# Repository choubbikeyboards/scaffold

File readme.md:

Scaffold keyboard
=================

This keyboard is inspired by many others, among which the Ferris, the Kyria, the Dactyl Manuform, and others.
The major contribution of this project is the method of using PCB for simultaneous structural support and electrical wiring of individual keys.

Status
------

This is still pretty much a prototype. The files I provide here have not yet been made into a PCB, although a previous version with minor changes has been tested successfully for some parts, and not so much for others.
Software side is not too advanced either, and you'll have to write your own QMK keymap.c file, as I didn't write a basic QWERTY keymap yet, and mine is pretty tuned to my personal use, with combos and stuff that works only for US-International OS-side layout.
The files for QMK can be found on my personal fork of QMK (https://github.com/choubbikeyboards/qmk_firmware/tree/master/keyboards/scaffold).

Important, read before ordering the PCBs!
-----------------------------------------

These boards need special ordering procedure, in order to just have to separate the smaller parts by hand. The fab must allow you to do V-scoring on your PCB. You must ask them to do V-scoring on all PCBs, by using the CMTS layer in the .zip files provided. This will tell the fab where to cut grooves into the PCB, to allow easy hand separation. This can be more expensive but saves a lot of time and possibly health, if you were to cut into the PCB yourself in your home (glass composite dust is nasty stuff for the lungs).
For more info about V-scoring, see this page.
Quick guide for an order on JLCPCB:
* Go to jlcpcb.com
* Click "Order now" button
* Click "Add gerber file" button, and select the .zip of one of the provided .zip files
* In "Delivery Format", click "Panel by customer", this should add a new option just below: "Panel Format"
* In "Panel Format", set the number of columns and row
    * 3 cols and 1 row for `scaffold.zip`
    * 1 col and 7 rows for `scaffold_supports.zip`
    * 6 cols and 6 rows for `scaffold_small_boards.zip`
* In "Remove Order Number", click "Specify a location", except for `scaffold_small_boards.zip`
* In "PCB Remark" (you need to click the pencil to access the text box), write this text: "Please V-score on Cmts layer". This will let the fab know that you want V-scoring and where to find it.

There are 3 different Kicad projects, all of these are necessary for a 3D scaffold build:
* `scaffold/` is the main PCB, and can be used as a standalone flat keyboard.
* `scaffold_supports/` is the angled supports that position the key above the main PCB. These are angled at 27°, the lowest I could get without problems.
* `scaffold_small_boards/` is the individual key footprints, with a Kailh low-profile and an SMD diode soldered in place. These are used for angled keys only, the flat keys have their diode soldered on the main board, and the switch inserted in a Kailh low-profile socket, soldered on the back of the main PCB.

Required parts
--------------

You will need as many of these as keys you want (for a full keys keyboard, that's 42 units):
* Kailh low-profile switches
* SMD diodes (I used SOD123 diodes)
* Keycaps

* As many Kailh low-profile hot-swap sockets as you want flat keys (including thumbs!)
* 2 ProMicro compatible boards
* 1 USB cable compatible with the ProMicro board you chose
* 2 push buttons, 6x6x4.3mm type
* 2 TRRS sockets, PJ-320A compatible footprint
* 1 TRRS cable
* either a custom case if you know how to make one, or 4mm thick adhesive silione feet (about 14 for the full keyboard).

Optional, for as many joysticks as you want:
* Joycon/Switch joysticks
* 5-pin 0.5mm pitch FPC/FFC connector
* something to attach the joystick to the board:
    * double-sided tape for thumb sticks
    * 2 screws, M1.6x5mm, and 2 M1.6 nuts per index stick. Double-sided tape work well too.

Optional, for each OLED screen you want:
* 4-pin 0.96 inch 128x64 OLED screen, SSD 1306 driver
* 2 resistors, value between 3 and 5kOhms (get 4.7k if you want a definite value)

Assembly guide
--------------

NOTE: This guide shows pictures of the version 1 of the keyboard. Current version (V2) uses inside soldering for the angled supports, both for the individual PCB and the main PCB. This shouldn't add much difficulty. This was done in order to get the whole PCB structure to interact better with the switches, as the previous version required the user to push hard on a switch to make it fit (slightly deforming the small plastic legs of the switch).

This is a quick overview of how to assemble a Scaffold keyboard. It shows only the right hand half, and skips the main components (MCU, OLED and its resistors...). It also shows a 3x5 configuration. For a 4x4-1 configuration, use the angled supports only for the top and bottom key of each column, and use hotswap sockets for the switches in between.

* Optional step: you can pre-tin the pads on the PCB pieces that you will solder on the board. The current version (V2 when I edit this guide) needs only one side of the angled pieces pre-tinned, and only the underside of the key holder pieces. Just be careful not to fill the switch pin holes when doing so.
* 1st step is to separate the pieces you'll need: each angled key needs 2 angled supports and an individual key holder.
* Then, start putting solder on one of the pads of each SMD diode, for the flat keys only (so 5 keys + thumbs here for a 3x5 configuration, 7 keys + thumbs for a 4x4-1 configuration)

* Once the solder is on one pad of a diode, place the diode on its footprint (white bar of the diode where the point of the triangle meets the other bar), solder one leg to the pre-soldered pad, and once the solder has cooled down, solder the other leg. Pre-soldering the pad makes it easier to solder the first leg without having to hold the soldering wire too. Keeping the other pad clean lets the diode leg rest against the PCB.

* Don't hesitate to turn the PCB around to access the pads more comfortably! 

* Now the SMD headers for the joysticks, if you plan on mounting one. This part is quite hard for me, so you will probably be best served by generic SMD soldering guides on your video website of choice. Anyway, I start by pre-soldering the pads. Be sure to check if there aren't any shorts at this stage, and don't use too much solder, or it will spread to the other pins when pushing the pin onto the solder in the later steps.

* Place the header on its footprint. That step requires accuracy to make the next step easier. Make sure the pins are properly aligned. Use a magnifying glass if needed (I can't do it without one myself).

* Solder the sides of the header first, and adjust the position of the header if it moved. Then solder the pins by pressing on them with the hot iron for a couple seconds and release. The solder placed earlier will normally stick to the pin and the pad, connecting them.

* Check for shorts, fix until no short remains... Have I mentioned I found this part hard?

* For each of the angled keys you need, solder the diode, like has been done on the main PCB for the flat keys. Again, trust the silkscreen to see which way to solder the diode.

* now, for each angled key, you have to build the support. Start with placing 2 angled supports in the slots of a key that is near the edge of the PCB. I prefer to build the supports where the supports are shown in the picture:

* Then, place the individual support on top, with the diode on top, but near the edge closest to the main PCB (towards the center of the main PCB on that picture). Then solder the inside connections on the highest point. This makes the angled support hold its own for soldering the other inner solder joints after removing the support from the main PCB.

* Take the angled support off the main PCB, solder the remaining inner joints. Try to keep the switch pin hole free for the next step.

* In the meantime, you can solder the hotswap sockets for the flat keys.

* Back to the angled holders: push the switch all the way in (requires a bit of force, but be careful not to bend a pin), and solder the pins to the small board.

* \[Version 2: soldering is now on the inside of the "box" to attach to the main PCB. Trickier, but fewer chances of shorting two adjacent switches together and better fit of the switch in the PCB\]
Now you have to solder the angled supports to the main PCB. The order of soldering can make things a bit simpler, but there will always remain a few tricky spots to solder.

* \[Version 2 solves this problem\]
Make sure to avoid soldering 2 adjacent switches together!

* Having the flat key switches off the board makes things easier.

* You now can place the switches in the hotswap sockets, solder the rest of the elements if it's not done already, and plug the joysticks in if needed. I used dual sided tape on angled supports for the thumb joysticks, just don't put a diode on those supports. Flat index joysticks can be taped to the main PCB the same way, or bolted in place with M1.6x5mm bolts.

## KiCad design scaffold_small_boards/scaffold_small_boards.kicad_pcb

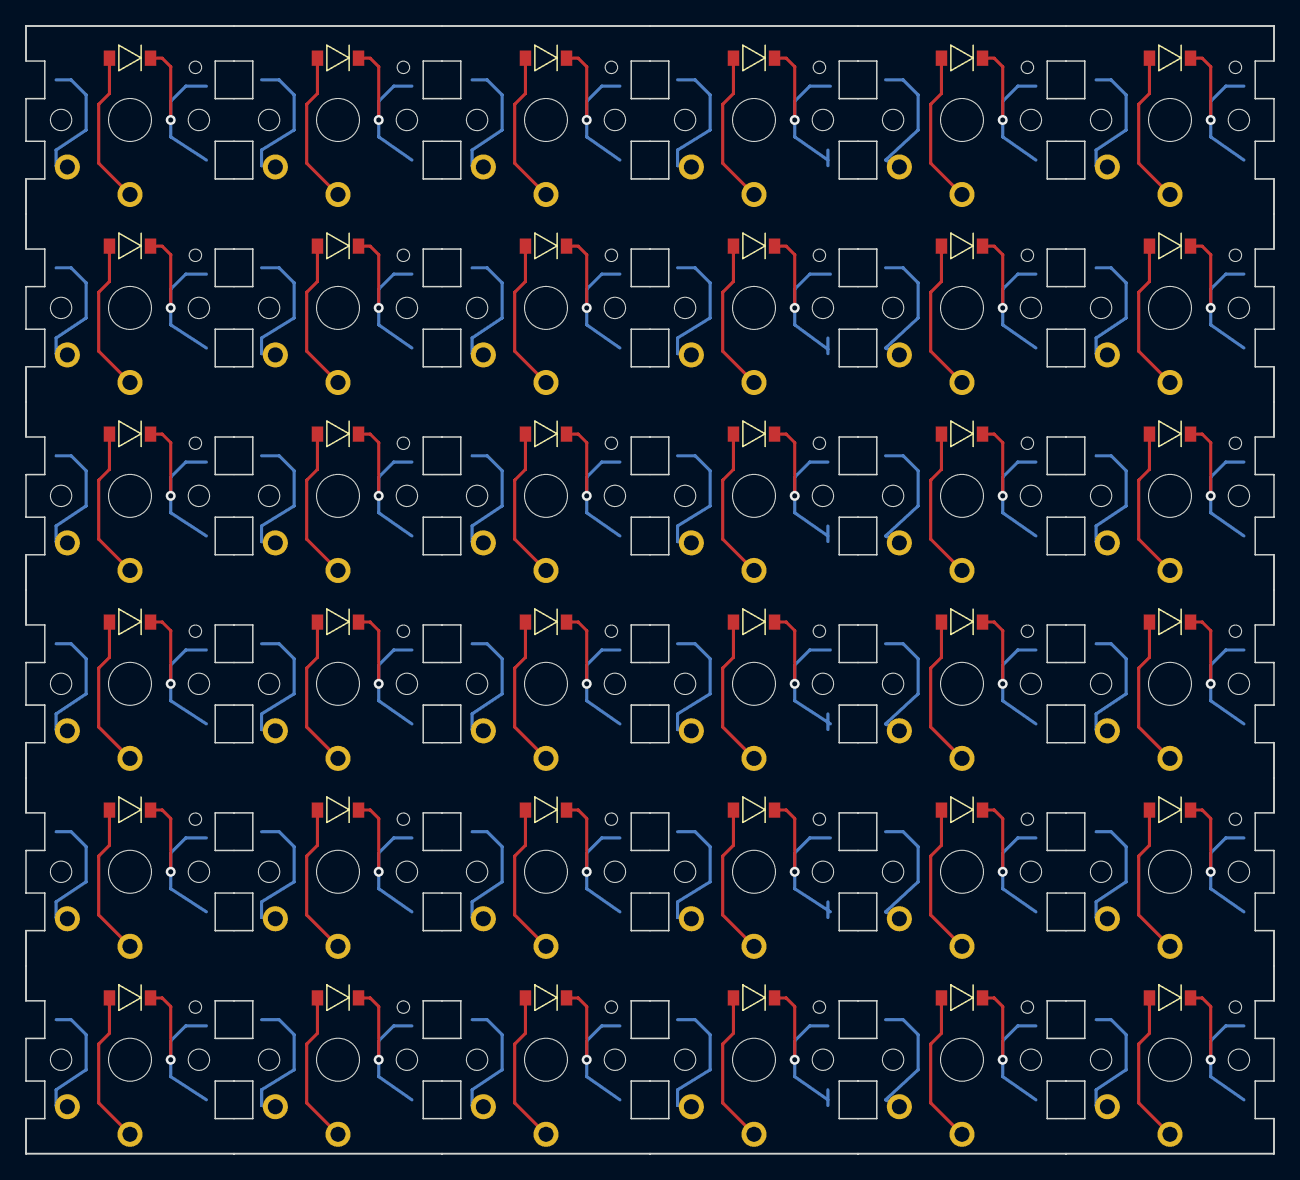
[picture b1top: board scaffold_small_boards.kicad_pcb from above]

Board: 2 copper layers, 99.6 x 90.0 mm, 36 parts (0 on the bottom side), 36 nets.

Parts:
SW_and_D1: SW_and_D; Kailh_PG1350_and_sod123_and_cutouts_top_left_v2
SW_and_D2, SW_and_D3, SW_and_D4, SW_and_D21: SW_and_D; Kailh_PG1350_and_sod123_and_cutouts_left_v2
SW_and_D5: SW_and_D; Kailh_PG1350_and_sod123_and_cutouts_bottom_left_v2
SW_and_D6, SW_and_D11, SW_and_D16, SW_and_D31: SW_and_D; Kailh_PG1350_and_sod123_and_cutouts_top_v2
SW_and_D7, SW_and_D8, SW_and_D9, SW_and_D12, SW_and_D13, SW_and_D14, SW_and_D17, SW_and_D18, SW_and_D19, SW_and_D25, SW_and_D26, SW_and_D27, SW_and_D28, SW_and_D29, SW_and_D30, SW_and_D32: SW_and_D; Kailh_PG1350_and_sod123_and_cutouts_center_v2
SW_and_D10, SW_and_D15, SW_and_D20, SW_and_D33: SW_and_D; Kailh_PG1350_and_sod123_and_cutouts_bottom_v2
SW_and_D22, SW_and_D23, SW_and_D24, SW_and_D35: SW_and_D; Kailh_PG1350_and_sod123_and_cutouts_right_v2
SW_and_D34: SW_and_D; Kailh_PG1350_and_sod123_and_cutouts_top_right_v2
SW_and_D36: SW_and_D; Kailh_PG1350_and_sod123_and_cutouts_bottom_right_v2

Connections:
unnamed: SW_and_D1.2, SW_and_D1.A
unnamed: SW_and_D2.2, SW_and_D2.A
unnamed: SW_and_D3.2, SW_and_D3.A
unnamed: SW_and_D4.2, SW_and_D4.A
unnamed: SW_and_D5.2, SW_and_D5.A
unnamed: SW_and_D6.2, SW_and_D6.A
unnamed: SW_and_D7.2, SW_and_D7.A
unnamed: SW_and_D8.2, SW_and_D8.A
unnamed: SW_and_D9.2, SW_and_D9.A
unnamed: SW_and_D10.2, SW_and_D10.A
unnamed: SW_and_D11.2, SW_and_D11.A
unnamed: SW_and_D12.2, SW_and_D12.A
unnamed: SW_and_D13.2, SW_and_D13.A
unnamed: SW_and_D14.2, SW_and_D14.A
unnamed: SW_and_D15.2, SW_and_D15.A
unnamed: SW_and_D16.2, SW_and_D16.A
unnamed: SW_and_D17.2, SW_and_D17.A
unnamed: SW_and_D18.2, SW_and_D18.A
unnamed: SW_and_D19.2, SW_and_D19.A
unnamed: SW_and_D20.2, SW_and_D20.A
unnamed: SW_and_D21.2, SW_and_D21.A
unnamed: SW_and_D22.2, SW_and_D22.A
unnamed: SW_and_D23.2, SW_and_D23.A
unnamed: SW_and_D24.2, SW_and_D24.A
unnamed: SW_and_D25.2, SW_and_D25.A
unnamed: SW_and_D26.2, SW_and_D26.A
unnamed: SW_and_D27.2, SW_and_D27.A
unnamed: SW_and_D28.2, SW_and_D28.A
unnamed: SW_and_D29.2, SW_and_D29.A
unnamed: SW_and_D30.2, SW_and_D30.A
unnamed: SW_and_D31.2, SW_and_D31.A
unnamed: SW_and_D32.2, SW_and_D32.A
unnamed: SW_and_D33.2, SW_and_D33.A
unnamed: SW_and_D34.2, SW_and_D34.A
unnamed: SW_and_D35.2, SW_and_D35.A
unnamed: SW_and_D36.2, SW_and_D36.A

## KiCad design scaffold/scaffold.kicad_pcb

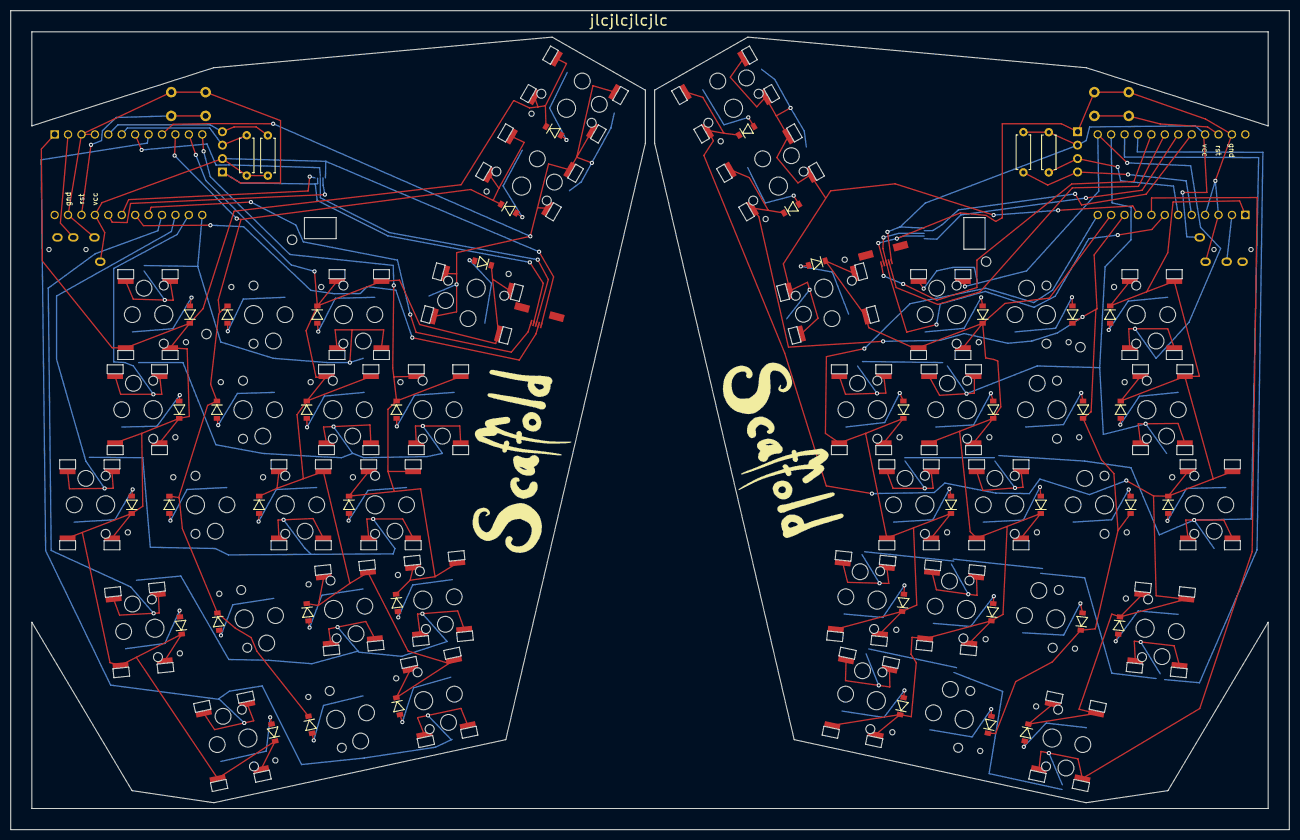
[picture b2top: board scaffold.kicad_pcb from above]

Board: 2 copper layers, 242.0 x 155.0 mm, 32 parts (0 on the bottom side), 84 nets.

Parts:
Col1, Col5: Col3; Col3_socket_PG1350_sod123_cutouts_v2
Col2, Col3, Col4: Col4; Col4_socket_PG1350_sod123_cutouts_v2
ColR1, ColR5: Col3; Col3_socket_PG1350_sod123_cutouts_v2
ColR2, ColR3, ColR4: Col4; Col4_socket_PG1350_sod123_cutouts_v2
J_TRRS_1, J_TRRS_2: AudioJack4; TRRS-PJ-320A
Joycon_index1, Joycon_index2: Joycon; joycon_flat_flex_cable_passing_through_pcb
Joycon_thumb1, Joycon_thumb2: Joycon; FPC_1x05-P0.5mm_Aliexpress
OLED1, OLED2: OLED; OLED_PinHeader_1x04_P2.54mm
R_SCL_1, R_SCL_2: 4.7k; R_Axial_DIN0207_L6.3mm_D2.5mm_P7.62mm_Horizontal
R_SDA_1, R_SDA_2: 4.7k; R_Axial_DIN0207_L6.3mm_D2.5mm_P7.62mm_Horizontal
SW1, SW2: SW_Push; SW_PUSH_6mm_H4.3mm_no_SilkS
SW_and_D1, SW_and_D2, SW_and_D3: SW_and_D; Col1_socket_PG1350_sod123_cutouts_v2
SW_and_DR1, SW_and_DR2, SW_and_DR3: SW_and_D; Col1_socket_PG1350_sod123_cutouts_v2
U1, U2: Pro_Micro; ProMicro_face_down

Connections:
+5V: J_TRRS_2.S, Joycon_index2.VCC, Joycon_thumb2.VCC, OLED2.VCC, R_SCL_2.1, R_SDA_2.2, U2.21
/COL_I1: Col4.a1, Col4.b1, Col4.m1, Col4.t1, U1.14
/COL_I2: Col5.b1, Col5.m1, Col5.t1, U1.13
/COL_M: Col3.a1, Col3.b1, Col3.m1, Col3.t1, U1.15
/COL_P: Col1.b1, Col1.m1, Col1.t1, U1.8
/COL_R: Col2.a1, Col2.b1, Col2.m1, Col2.t1, U1.16
/COL_RI1: ColR4.a1, ColR4.b1, ColR4.m1, ColR4.t1, U2.14
/COL_RI2: ColR5.b1, ColR5.m1, ColR5.t1, U2.13
/COL_RM: ColR3.a1, ColR3.b1, ColR3.m1, ColR3.t1, U2.15
/COL_RP: ColR1.b1, ColR1.m1, ColR1.t1, U2.8
/COL_RR: ColR2.a1, ColR2.b1, ColR2.m1, ColR2.t1, U2.16
/COL_RT: SW_and_DR1.1, SW_and_DR2.1, SW_and_DR3.1, U2.9
/COL_T: SW_and_D1.1, SW_and_D2.1, SW_and_D3.1, U1.9
/JOYCON_LR1: Joycon_thumb1.Left_Right, U1.17
/JOYCON_LR2: Joycon_index1.Left_Right, U1.19
/JOYCON_Push: Joycon_index1.Push_button, Joycon_thumb1.Push_button, U1.7
/JOYCON_R_LR1: Joycon_thumb2.Left_Right, U2.17
/JOYCON_R_LR2: Joycon_index2.Left_Right, U2.19
/JOYCON_R_Push: Joycon_index2.Push_button, Joycon_thumb2.Push_button, U2.7
/JOYCON_R_UD1: Joycon_thumb2.Up_Down, U2.18
/JOYCON_R_UD2: Joycon_index2.Up_Down, U2.20
/JOYCON_UD1: Joycon_thumb1.Up_Down, U1.18
/JOYCON_UD2: Joycon_index1.Up_Down, U1.20
/ROW_ADD: Col2.aK, Col3.aK, Col4.aK, U1.12
/ROW_B: Col1.bK, Col2.bK, Col3.bK, Col4.bK, Col5.bK, SW_and_D3.K, U1.11
/ROW_M: Col1.mK, Col2.mK, Col3.mK, Col4.mK, Col5.mK, SW_and_D2.K, U1.10
/ROW_RADD: ColR2.aK, ColR3.aK, ColR4.aK, U2.12
/ROW_RB: ColR1.bK, ColR2.bK, ColR3.bK, ColR4.bK, ColR5.bK, SW_and_DR3.K, U2.11
/ROW_RM: ColR1.mK, ColR2.mK, ColR3.mK, ColR4.mK, ColR5.mK, SW_and_DR2.K, U2.10
/ROW_RT: ColR1.tK, ColR2.tK, ColR3.tK, ColR4.tK, ColR5.tK, SW_and_DR1.K, U2.1
/ROW_T: Col1.tK, Col2.tK, Col3.tK, Col4.tK, Col5.tK, SW_and_D1.K, U1.1
/RST: SW1.2, U1.22
/RST_R: SW2.2, U2.22
/SCL: OLED1.SCL, R_SCL_1.2, U1.6
/SCL_R: OLED2.SCL, R_SCL_2.2, U2.6
/SDA: OLED1.SDA, R_SDA_1.1, U1.5
/SDA_R: OLED2.SDA, R_SDA_2.1, U2.5
/SERIAL: J_TRRS_1.R1, U1.2
/SERIAL_R: J_TRRS_2.R1, U2.2
GND: J_TRRS_1.T, Joycon_index1.GND, Joycon_thumb1.GND, OLED1.GND, SW1.1, U1.3, U1.4, U1.23
GNDD: J_TRRS_2.T, Joycon_index2.GND, Joycon_thumb2.GND, OLED2.GND, SW2.1, U2.3, U2.4, U2.23
unnamed: Col1.b2, Col1.bA
unnamed: Col1.m2, Col1.mA
unnamed: Col1.t2, Col1.tA
unnamed: Col2.a2, Col2.aA
unnamed: Col2.b2, Col2.bA
unnamed: Col2.m2, Col2.mA
unnamed: Col2.t2, Col2.tA
unnamed: Col3.a2, Col3.aA
unnamed: Col3.b2, Col3.bA
unnamed: Col3.m2, Col3.mA
unnamed: Col3.t2, Col3.tA
unnamed: Col4.a2, Col4.aA
unnamed: Col4.b2, Col4.bA
unnamed: Col4.m2, Col4.mA
unnamed: Col4.t2, Col4.tA
unnamed: Col5.b2, Col5.bA
unnamed: Col5.m2, Col5.mA
unnamed: Col5.t2, Col5.tA
unnamed: ColR1.b2, ColR1.bA
unnamed: ColR1.m2, ColR1.mA
unnamed: ColR1.t2, ColR1.tA
unnamed: ColR2.a2, ColR2.aA
unnamed: ColR2.b2, ColR2.bA
unnamed: ColR2.m2, ColR2.mA
unnamed: ColR2.t2, ColR2.tA
unnamed: ColR3.a2, ColR3.aA
unnamed: ColR3.b2, ColR3.bA
unnamed: ColR3.m2, ColR3.mA
unnamed: ColR3.t2, ColR3.tA
unnamed: ColR4.a2, ColR4.aA
unnamed: ColR4.b2, ColR4.bA
unnamed: ColR4.m2, ColR4.mA
unnamed: ColR4.t2, ColR4.tA
unnamed: ColR5.b2, ColR5.bA
unnamed: ColR5.m2, ColR5.mA
unnamed: ColR5.t2, ColR5.tA
unnamed: SW_and_D1.2, SW_and_D1.A
unnamed: SW_and_D2.2, SW_and_D2.A
unnamed: SW_and_D3.2, SW_and_D3.A
unnamed: SW_and_DR1.2, SW_and_DR1.A
unnamed: SW_and_DR2.2, SW_and_DR2.A
unnamed: SW_and_DR3.2, SW_and_DR3.A
VCC: J_TRRS_1.S, Joycon_index1.VCC, Joycon_thumb1.VCC, OLED1.VCC, R_SCL_1.1, R_SDA_1.2, U1.21

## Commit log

2021-08-22 First commit in scaffold repo. V1, OLED not properly tested. Use at your own risk!
2021-08-22 Add readme
2021-08-22 Add tape/bolts to readme
2021-08-23 Add picture
2021-09-18 Update readme with assembly tutorial
2021-09-18 Fix image links
2021-09-18 Fix image alignment
2021-10-28 Add main board projects for separate PCBs (left/right halves are 2 separate projects)
2022-02-14 Scaffold V2: wider spacing for supports for better switch fit, updated assembly guide.
2022-02-14 Scaffold V2: remove individual board project files, as they are now incompatible with the individual switch supports
